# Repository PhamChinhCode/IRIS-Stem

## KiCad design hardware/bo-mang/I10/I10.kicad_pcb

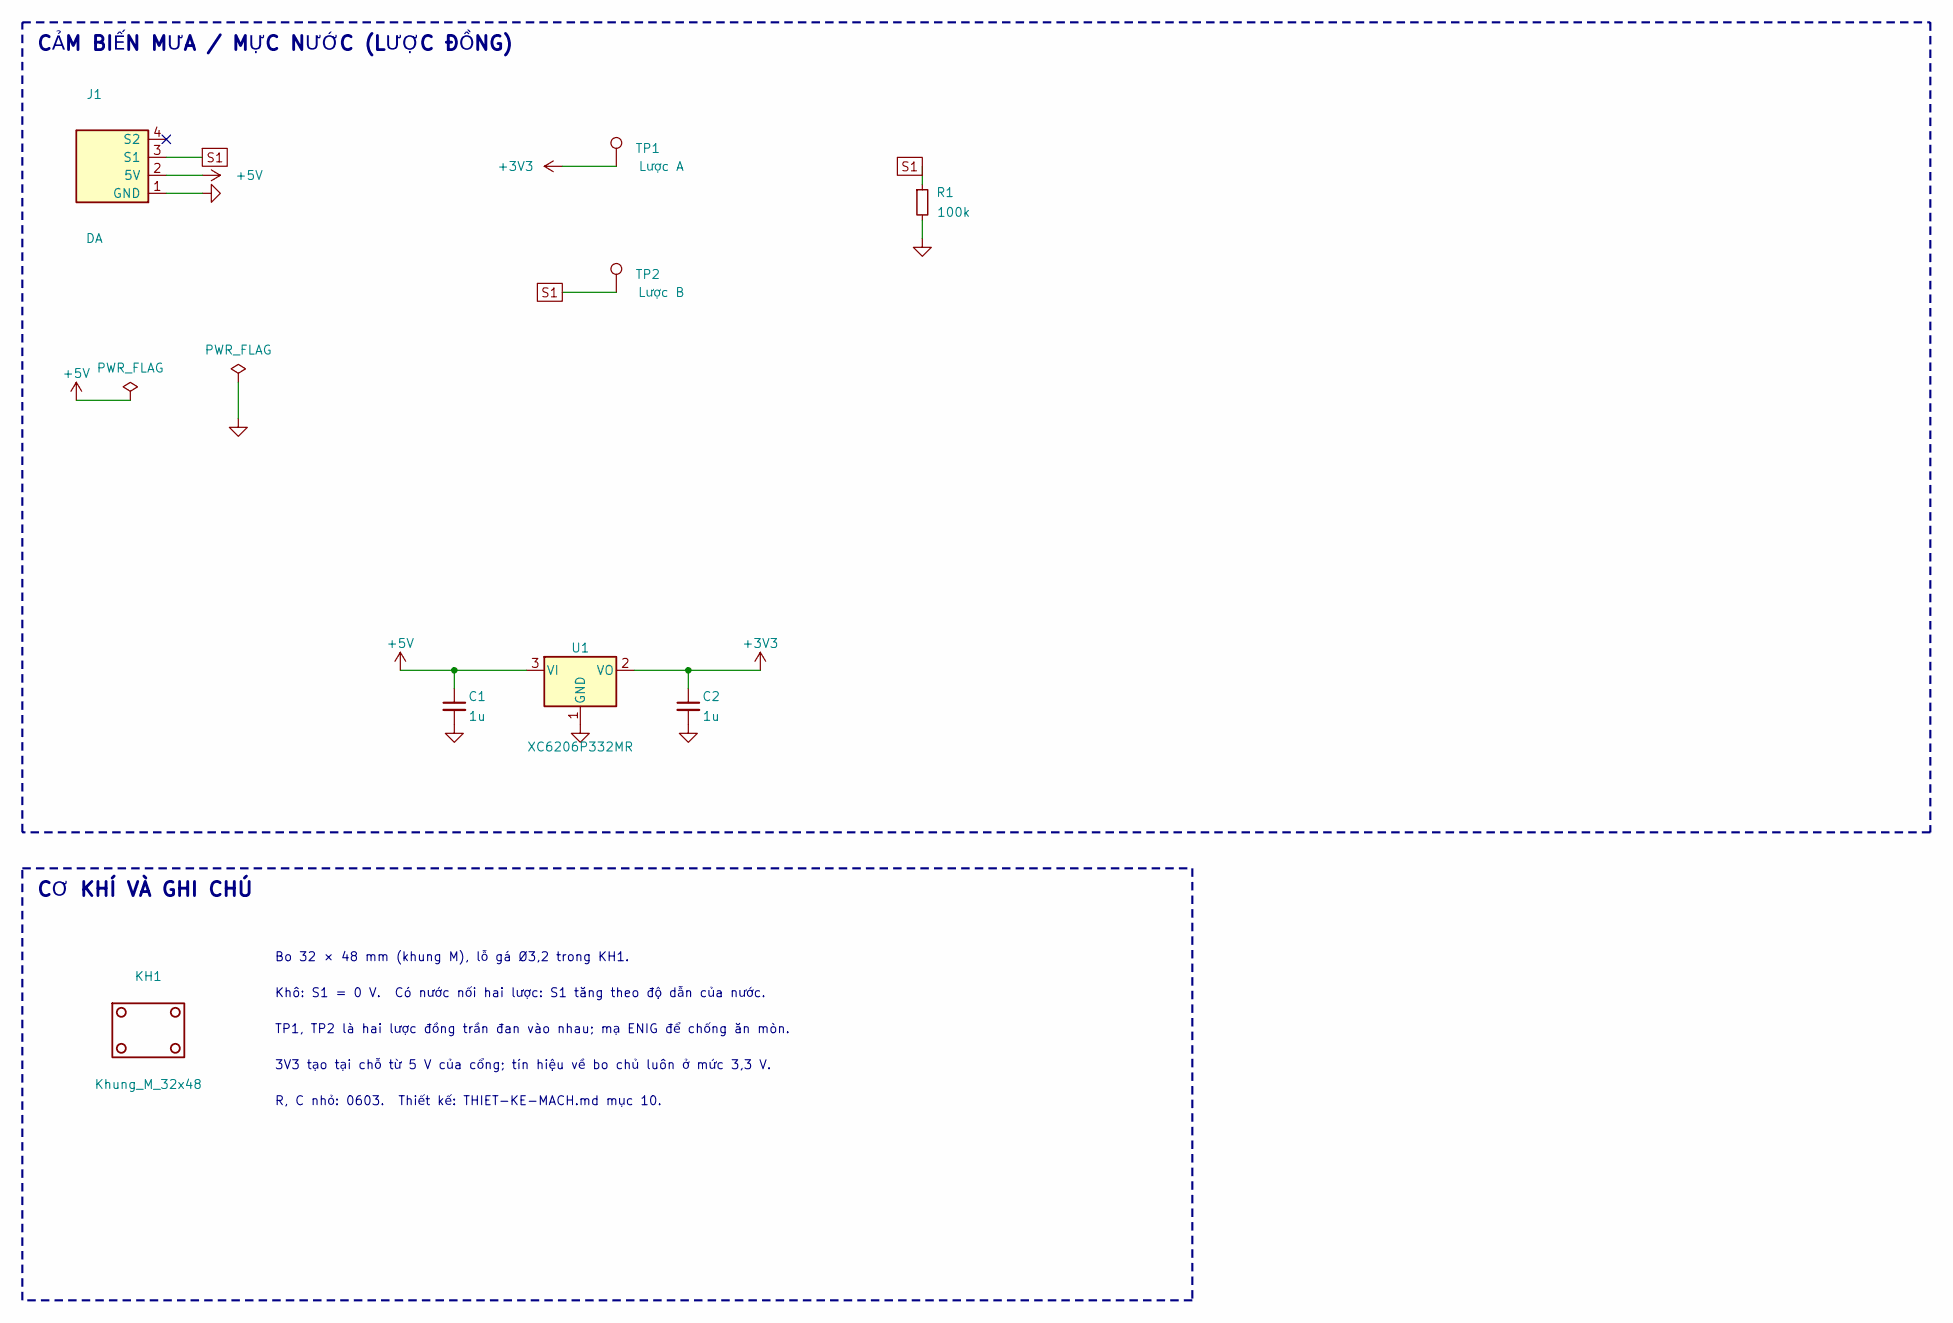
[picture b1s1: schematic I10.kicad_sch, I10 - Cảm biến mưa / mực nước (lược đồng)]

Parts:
C1, C2: 1u; C_0603_1608Metric
J1: DA; Cong_PH_4P_Ngang
KH1: Khung_M_32x48
R1: 100k; R_0603_1608Metric
TP1: Lược A; TestPoint_Pad_D1.5mm
TP2: Lược B; TestPoint_Pad_D1.5mm
U1: XC6206P332MR; SOT-23-3; MPN XC6206P332MR

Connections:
+3V3: C2.1, TP1.1, U1.2 (VO)
+5V: C1.1, J1.2 (5V), U1.3 (VI)
GND: C1.2, C2.2, J1.1 (GND), R1.2, U1.1 (GND)
S1: J1.3 (S1), R1.1, TP2.1

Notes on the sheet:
CẢM BIẾN MƯA / MỰC NƯỚC (LƯỢC ĐỒNG)
CƠ KHÍ VÀ GHI CHÚ
Bo 32 × 48 mm (khung M), lỗ gá Ø3,2 trong KH1.
Khô: S1 = 0 V. Có nước nối hai lược: S1 tăng theo độ dẫn của nước.
TP1, TP2 là hai lược đồng trần đan vào nhau; mạ ENIG để chống ăn mòn.
3V3 tạo tại chỗ từ 5 V của cổng; tín hiệu về bo chủ luôn ở mức 3,3 V.
R, C nhỏ: 0603. Thiết kế: THIET-KE-MACH.md mục 10.

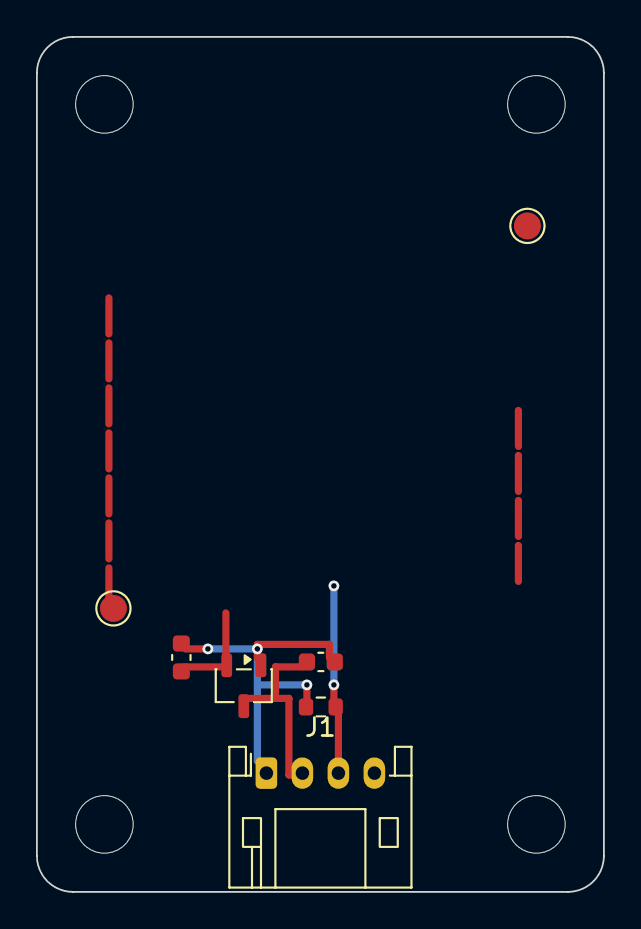
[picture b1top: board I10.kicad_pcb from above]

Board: 2 copper layers, 31.5 x 47.5 mm, 8 parts (0 on the bottom side), 4 nets.

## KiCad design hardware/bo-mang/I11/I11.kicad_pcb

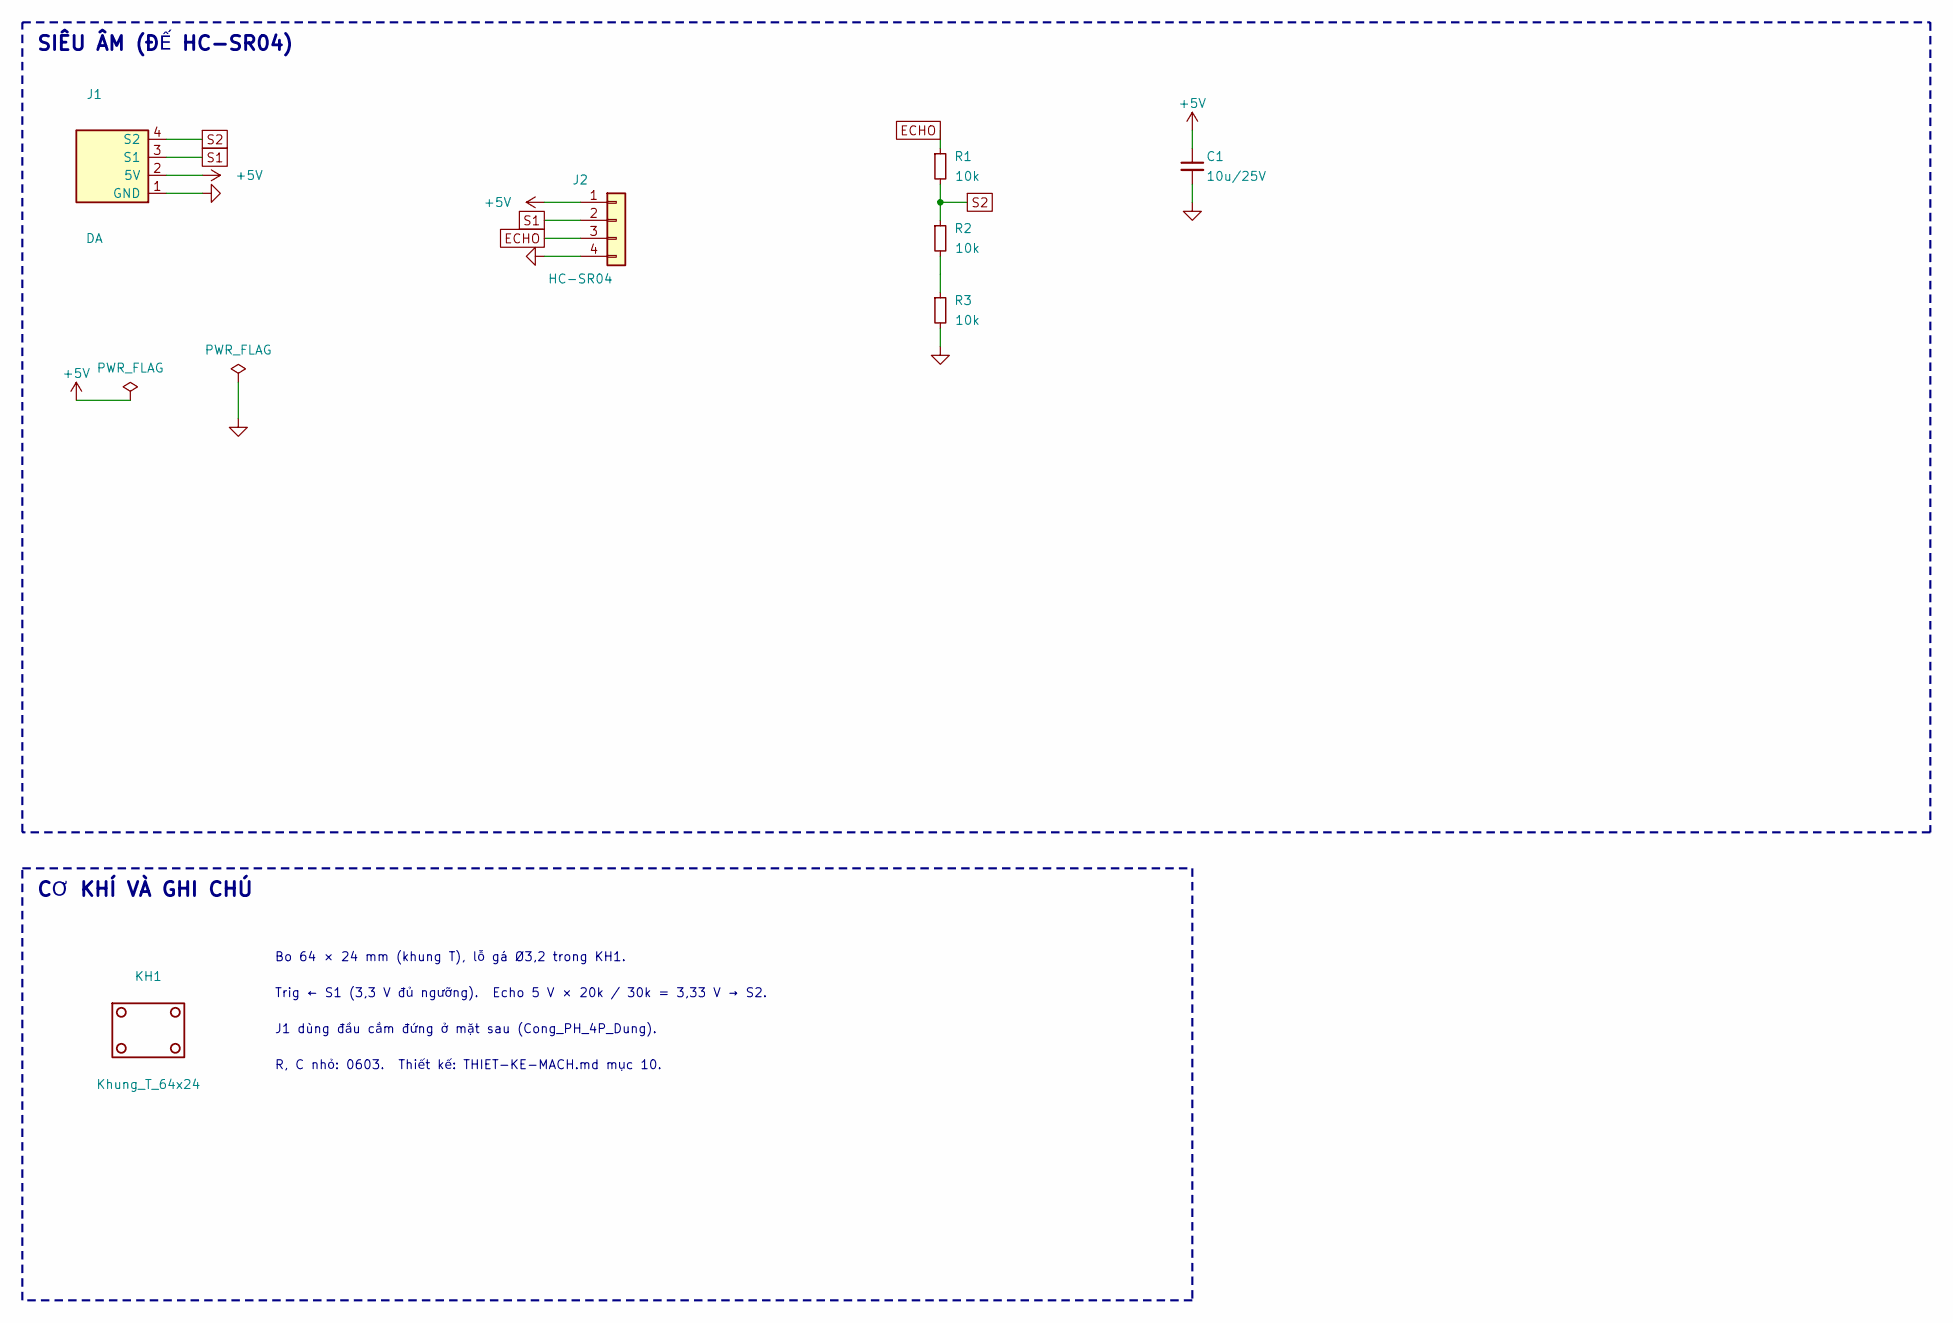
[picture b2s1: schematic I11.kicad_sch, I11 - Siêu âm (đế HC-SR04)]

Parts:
C1: 10u/25V; C_0805_2012Metric
J1: DA; Cong_PH_4P_Dung
J2: HC-SR04; PinSocket_1x04_P2.54mm_Vertical
KH1: Khung_T_64x24
R1, R2, R3: 10k; R_0603_1608Metric

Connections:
+5V: C1.1, J1.2 (5V), J2.1
ECHO: J2.3, R1.1
GND: C1.2, J1.1 (GND), J2.4, R3.2
unnamed: R2.2, R3.1
S1: J1.3 (S1), J2.2
S2: J1.4 (S2), R1.2, R2.1

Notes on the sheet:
SIÊU ÂM (ĐẾ HC-SR04)
CƠ KHÍ VÀ GHI CHÚ
Bo 64 × 24 mm (khung T), lỗ gá Ø3,2 trong KH1.
Trig ← S1 (3,3 V đủ ngưỡng). Echo 5 V × 20k / 30k = 3,33 V → S2.
J1 dùng đầu cắm đứng ở mặt sau (Cong_PH_4P_Dung).
R, C nhỏ: 0603. Thiết kế: THIET-KE-MACH.md mục 10.

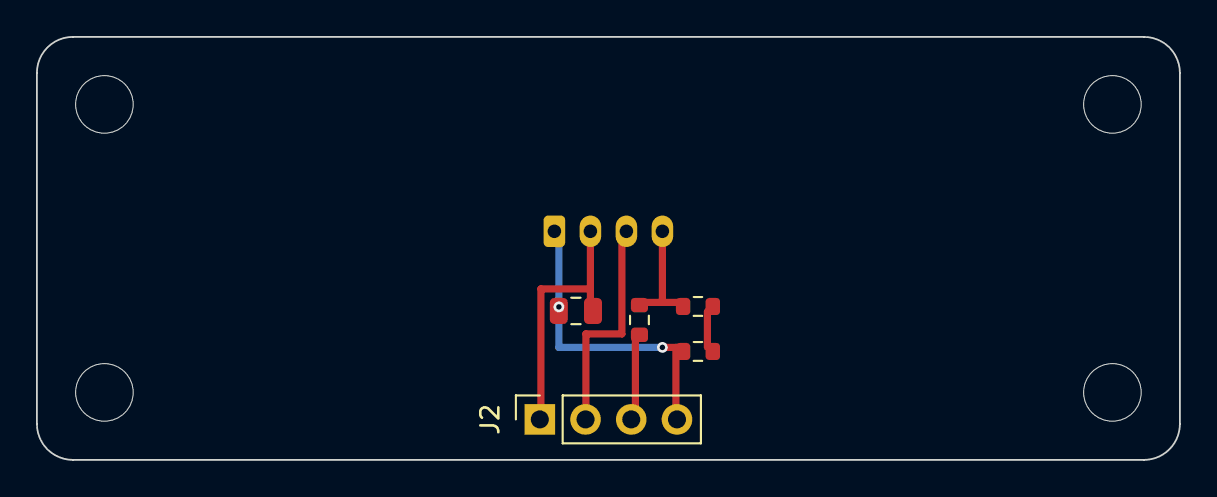
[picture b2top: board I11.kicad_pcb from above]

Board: 2 copper layers, 63.5 x 23.5 mm, 7 parts (1 on the bottom side), 6 nets.

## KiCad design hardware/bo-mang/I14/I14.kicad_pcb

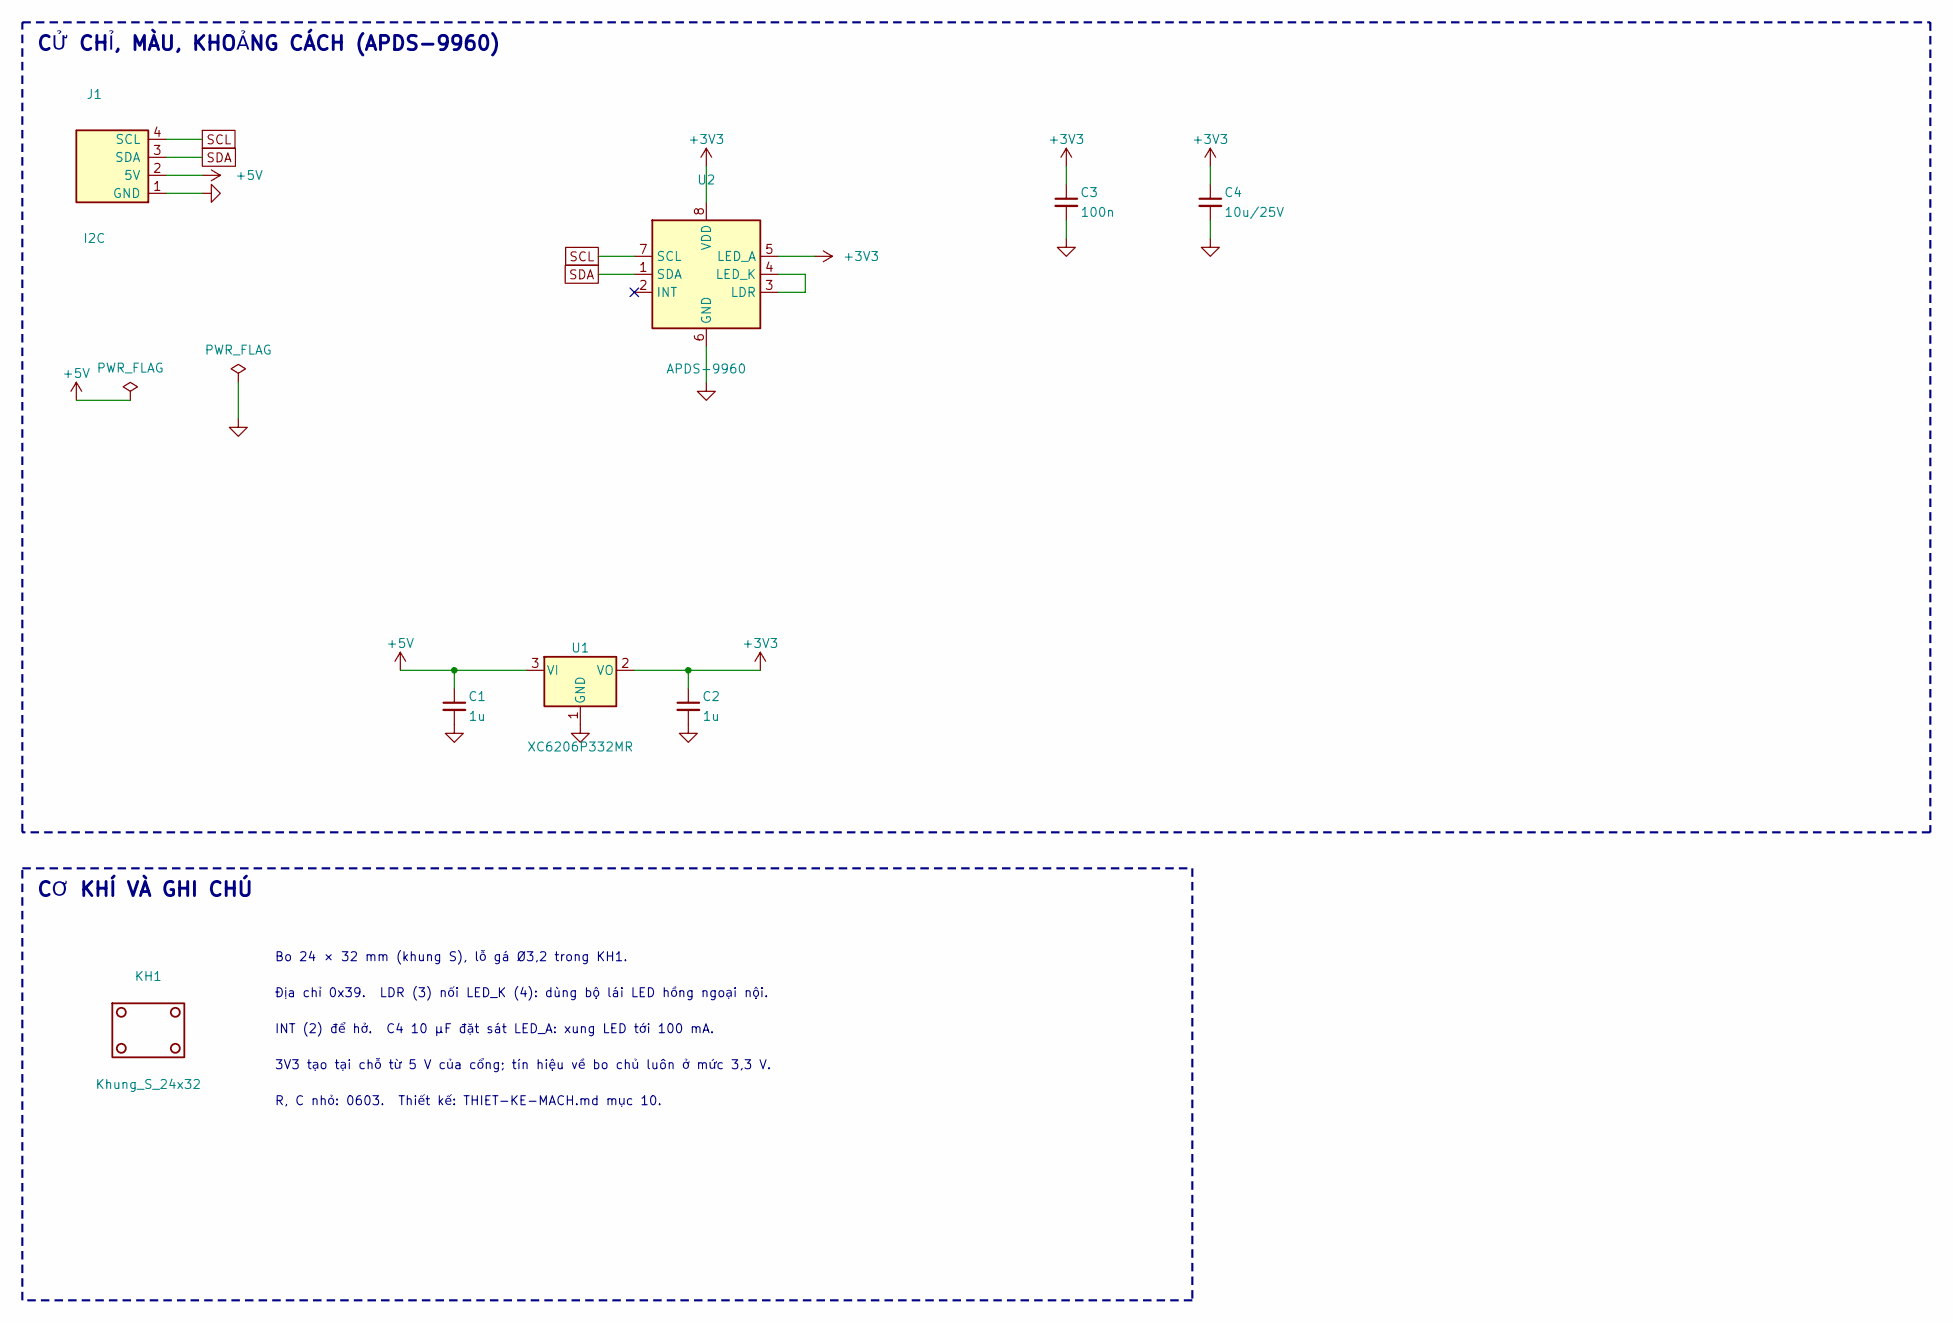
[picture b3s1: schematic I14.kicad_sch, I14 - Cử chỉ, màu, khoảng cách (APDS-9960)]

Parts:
C1, C2: 1u; C_0603_1608Metric
C3: 100n; C_0603_1608Metric
C4: 10u/25V; C_0805_2012Metric
J1: I2C; Cong_PH_4P_Ngang
KH1: Khung_S_24x32
U1: XC6206P332MR; SOT-23-3; MPN XC6206P332MR
U2: APDS-9960; Avago_APDS-9960; MPN APDS-9960

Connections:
+3V3: C2.1, C3.1, C4.1, U1.2 (VO), U2.5 (LED_A), U2.8 (VDD)
+5V: C1.1, J1.2 (5V), U1.3 (VI)
GND: C1.2, C2.2, C3.2, C4.2, J1.1 (GND), U1.1 (GND), U2.6 (GND)
unnamed: U2.3 (LDR), U2.4 (LED_K)
SCL: J1.4 (SCL), U2.7 (SCL)
SDA: J1.3 (SDA), U2.1 (SDA)

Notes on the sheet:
CỬ CHỈ, MÀU, KHOẢNG CÁCH (APDS-9960)
CƠ KHÍ VÀ GHI CHÚ
Bo 24 × 32 mm (khung S), lỗ gá Ø3,2 trong KH1.
Địa chỉ 0x39. LDR (3) nối LED_K (4): dùng bộ lái LED hồng ngoại nội.
INT (2) để hở. C4 10 µF đặt sát LED_A: xung LED tới 100 mA.
3V3 tạo tại chỗ từ 5 V của cổng; tín hiệu về bo chủ luôn ở mức 3,3 V.
R, C nhỏ: 0603. Thiết kế: THIET-KE-MACH.md mục 10.

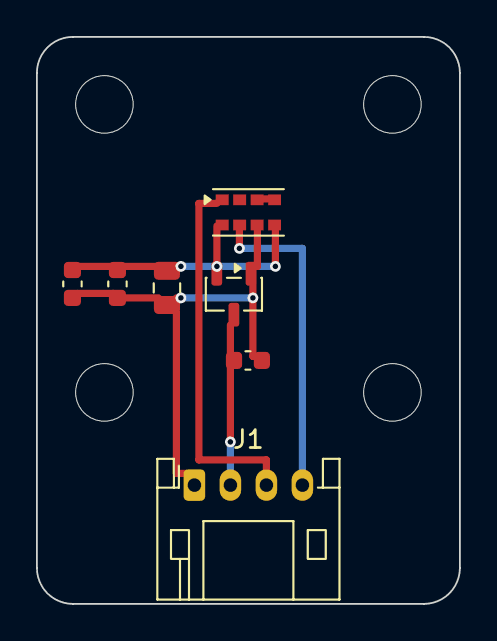
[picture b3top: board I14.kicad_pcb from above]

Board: 2 copper layers, 23.5 x 31.5 mm, 8 parts (0 on the bottom side), 6 nets.

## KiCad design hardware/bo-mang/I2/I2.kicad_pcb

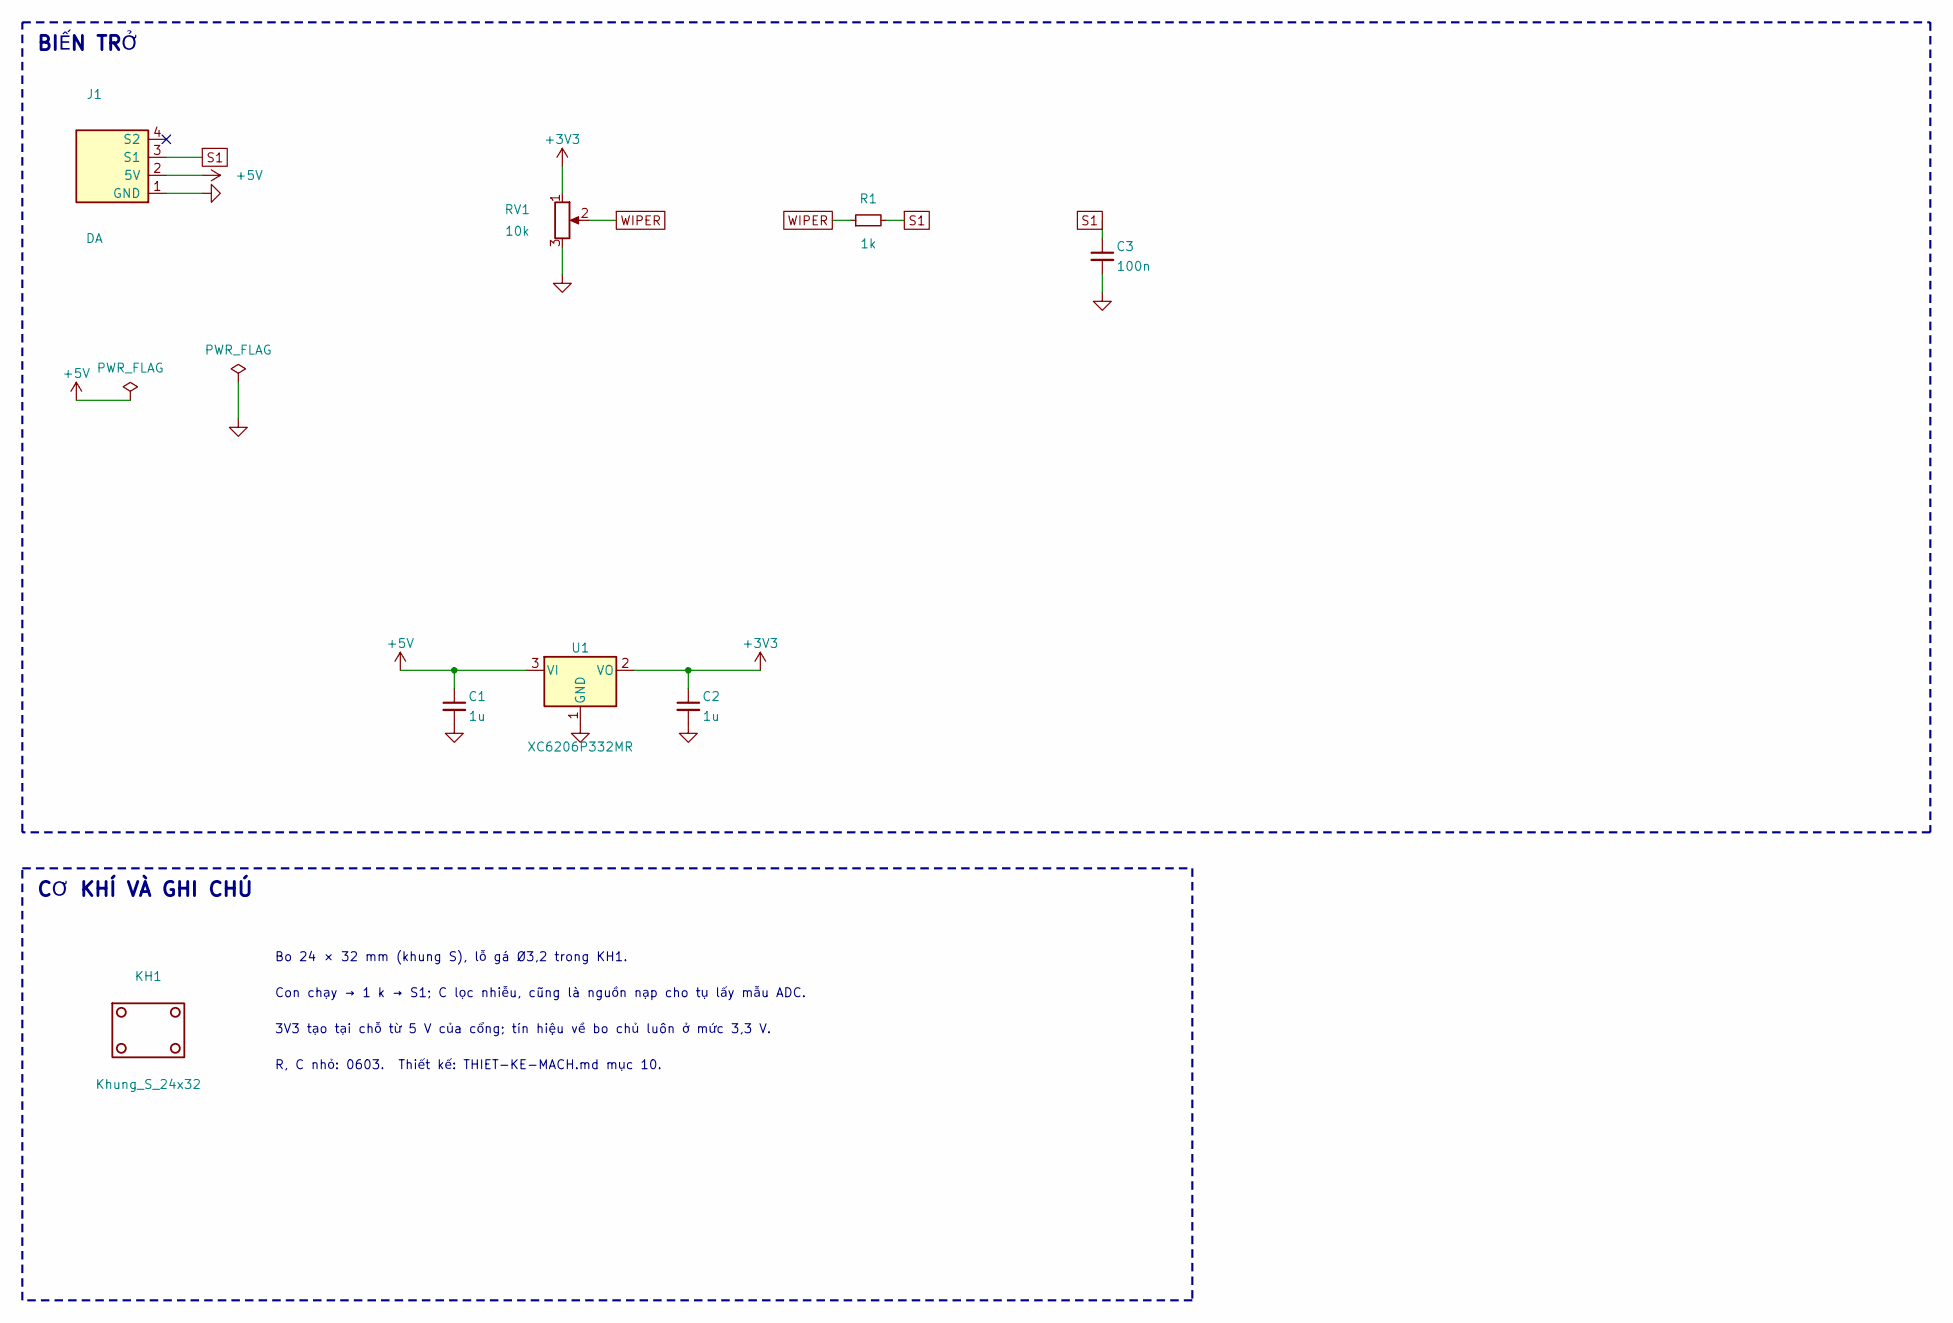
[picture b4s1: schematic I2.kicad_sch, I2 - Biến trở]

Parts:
C1, C2: 1u; C_0603_1608Metric
C3: 100n; C_0603_1608Metric
J1: DA; Cong_PH_4P_Ngang
KH1: Khung_S_24x32
R1: 1k; R_0603_1608Metric
RV1: 10k; Potentiometer_Alps_RK09K_Single_Vertical
U1: XC6206P332MR; SOT-23-3; MPN XC6206P332MR

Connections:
+3V3: C2.1, RV1.1, U1.2 (VO)
+5V: C1.1, J1.2 (5V), U1.3 (VI)
GND: C1.2, C2.2, C3.2, J1.1 (GND), RV1.3, U1.1 (GND)
S1: C3.1, J1.3 (S1), R1.2
WIPER: R1.1, RV1.2

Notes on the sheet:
BIẾN TRỞ
CƠ KHÍ VÀ GHI CHÚ
Bo 24 × 32 mm (khung S), lỗ gá Ø3,2 trong KH1.
Con chạy → 1 k → S1; C lọc nhiễu, cũng là nguồn nạp cho tụ lấy mẫu ADC.
3V3 tạo tại chỗ từ 5 V của cổng; tín hiệu về bo chủ luôn ở mức 3,3 V.
R, C nhỏ: 0603. Thiết kế: THIET-KE-MACH.md mục 10.

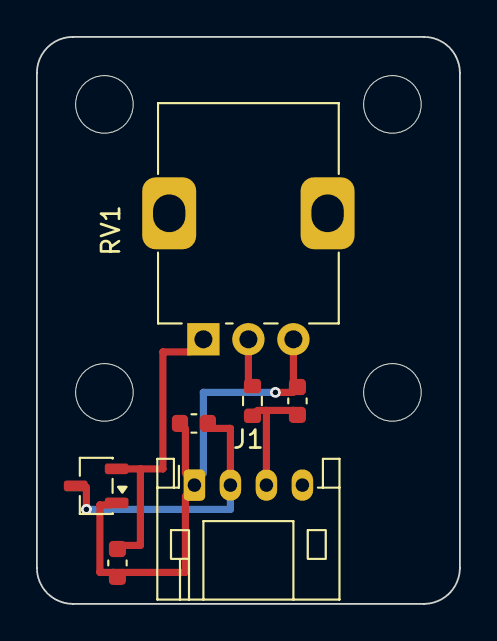
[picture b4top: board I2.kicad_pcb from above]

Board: 2 copper layers, 23.5 x 31.5 mm, 8 parts (0 on the bottom side), 5 nets.

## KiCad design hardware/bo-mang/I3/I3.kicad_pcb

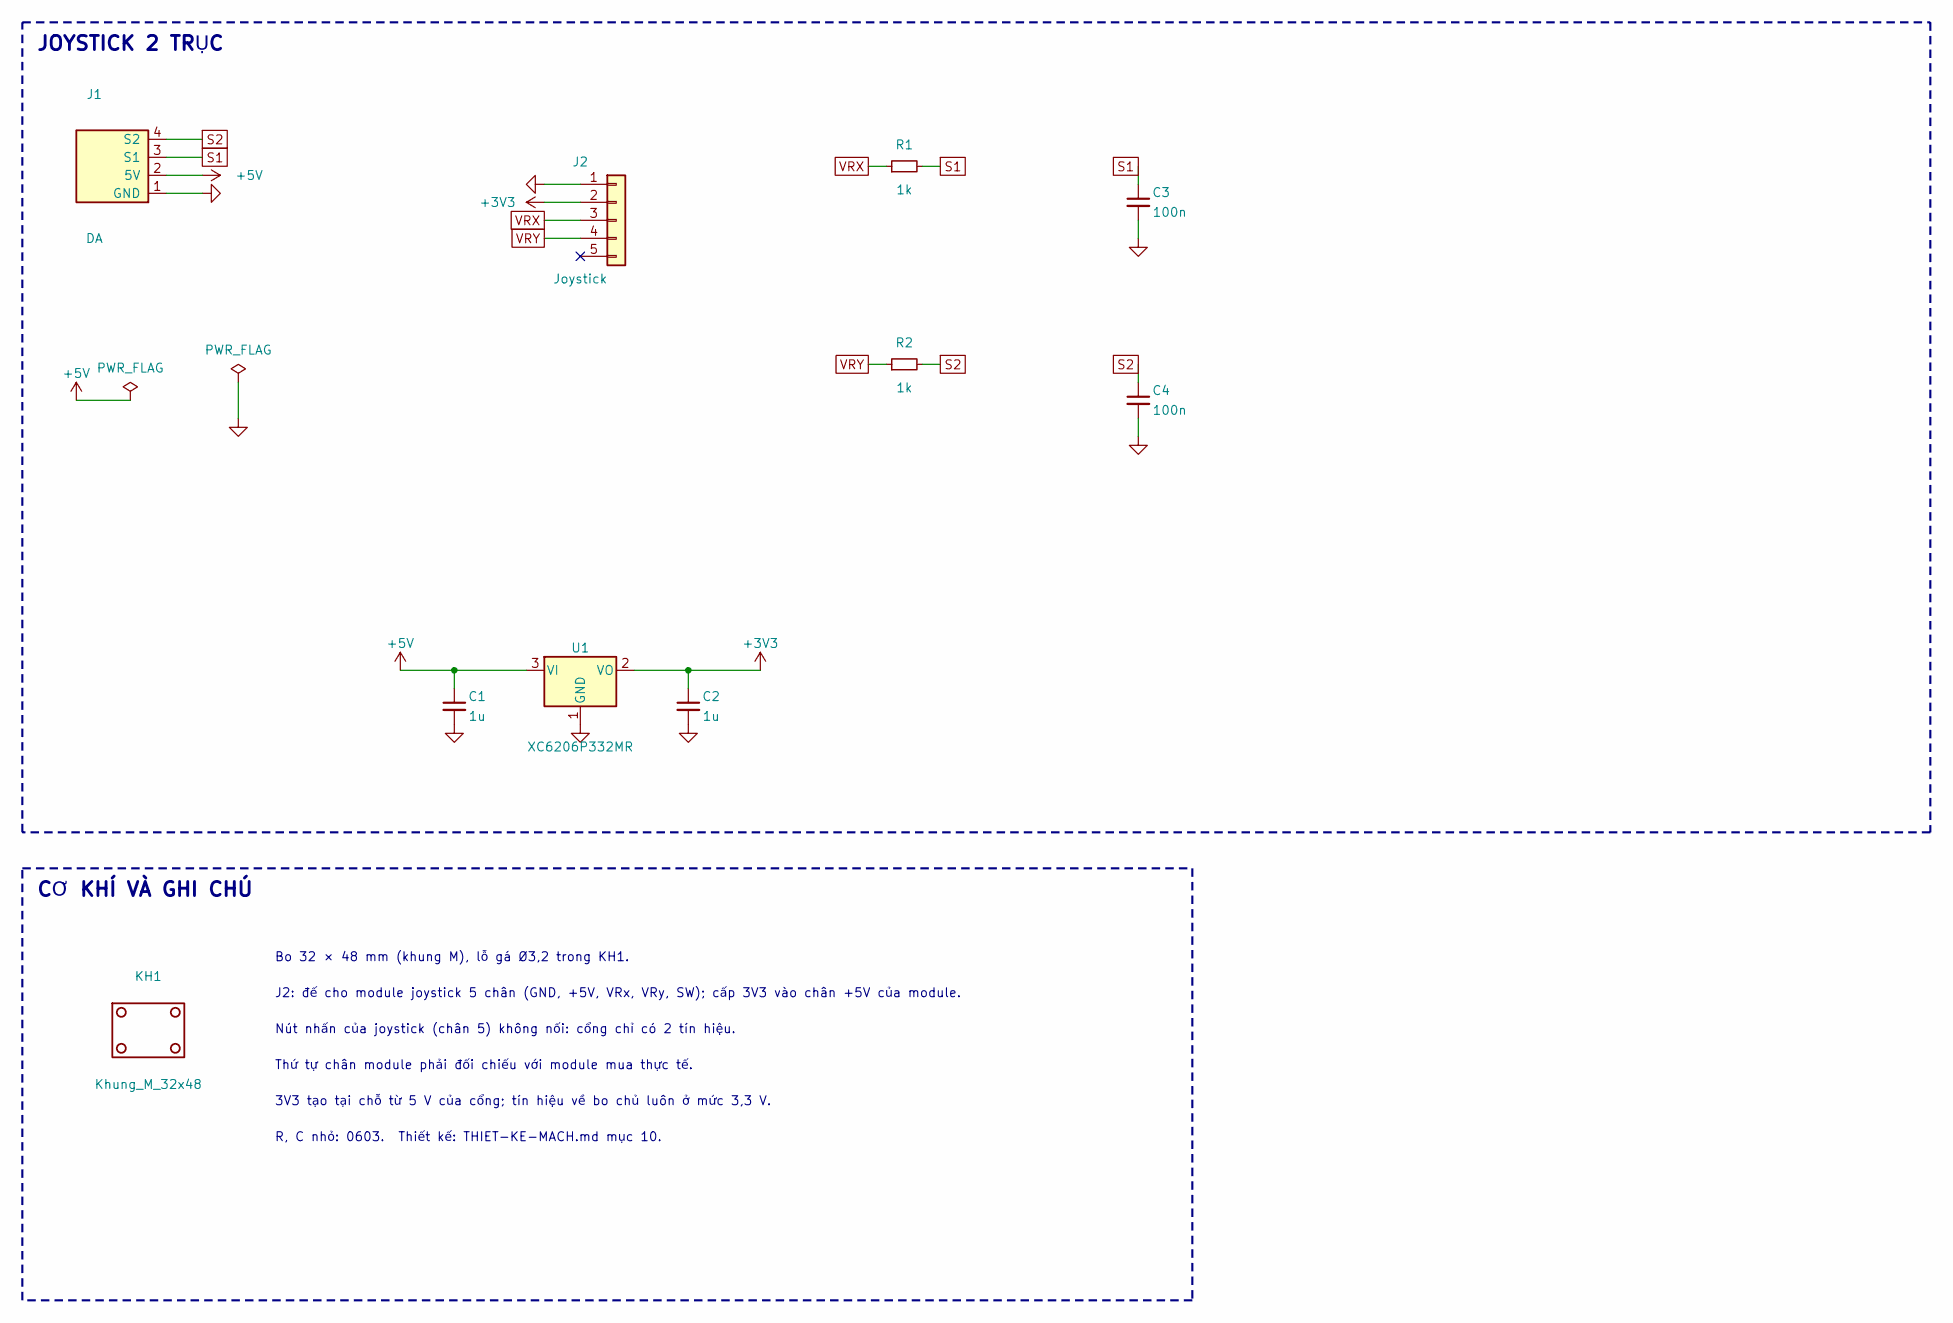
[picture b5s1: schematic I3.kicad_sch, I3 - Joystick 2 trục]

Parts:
C1, C2: 1u; C_0603_1608Metric
C3, C4: 100n; C_0603_1608Metric
J1: DA; Cong_PH_4P_Ngang
J2: Joystick; PinSocket_1x05_P2.54mm_Vertical
KH1: Khung_M_32x48
R1, R2: 1k; R_0603_1608Metric
U1: XC6206P332MR; SOT-23-3; MPN XC6206P332MR

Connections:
+3V3: C2.1, J2.2, U1.2 (VO)
+5V: C1.1, J1.2 (5V), U1.3 (VI)
GND: C1.2, C2.2, C3.2, C4.2, J1.1 (GND), J2.1, U1.1 (GND)
S1: C3.1, J1.3 (S1), R1.2
S2: C4.1, J1.4 (S2), R2.2
VRX: J2.3, R1.1
VRY: J2.4, R2.1

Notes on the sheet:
JOYSTICK 2 TRỤC
CƠ KHÍ VÀ GHI CHÚ
Bo 32 × 48 mm (khung M), lỗ gá Ø3,2 trong KH1.
J2: đế cho module joystick 5 chân (GND, +5V, VRx, VRy, SW); cấp 3V3 vào chân +5V của module.
Nút nhấn của joystick (chân 5) không nối: cổng chỉ có 2 tín hiệu.
Thứ tự chân module phải đối chiếu với module mua thực tế.
3V3 tạo tại chỗ từ 5 V của cổng; tín hiệu về bo chủ luôn ở mức 3,3 V.
R, C nhỏ: 0603. Thiết kế: THIET-KE-MACH.md mục 10.

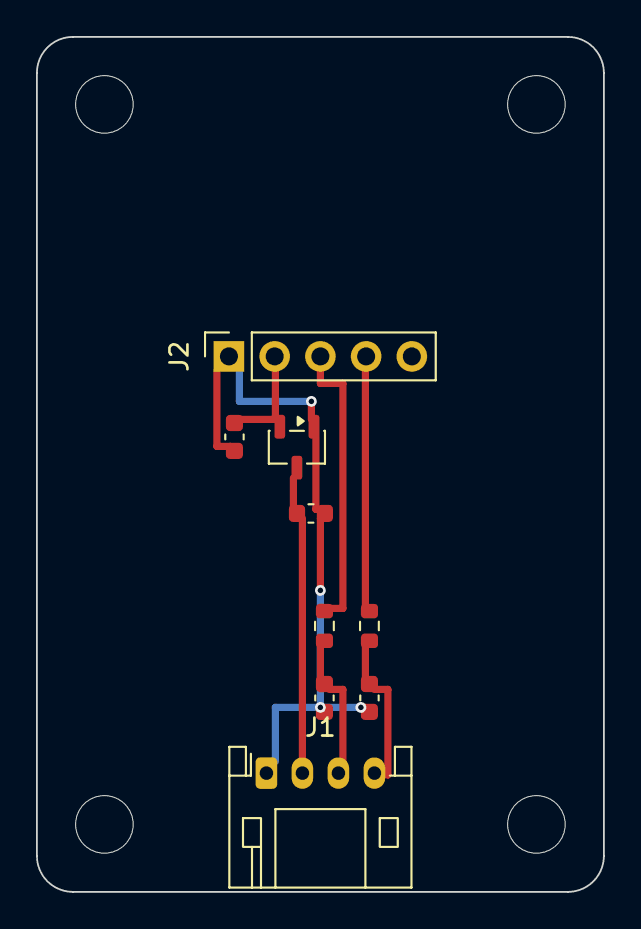
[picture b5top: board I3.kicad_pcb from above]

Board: 2 copper layers, 31.5 x 47.5 mm, 10 parts (0 on the bottom side), 7 nets.

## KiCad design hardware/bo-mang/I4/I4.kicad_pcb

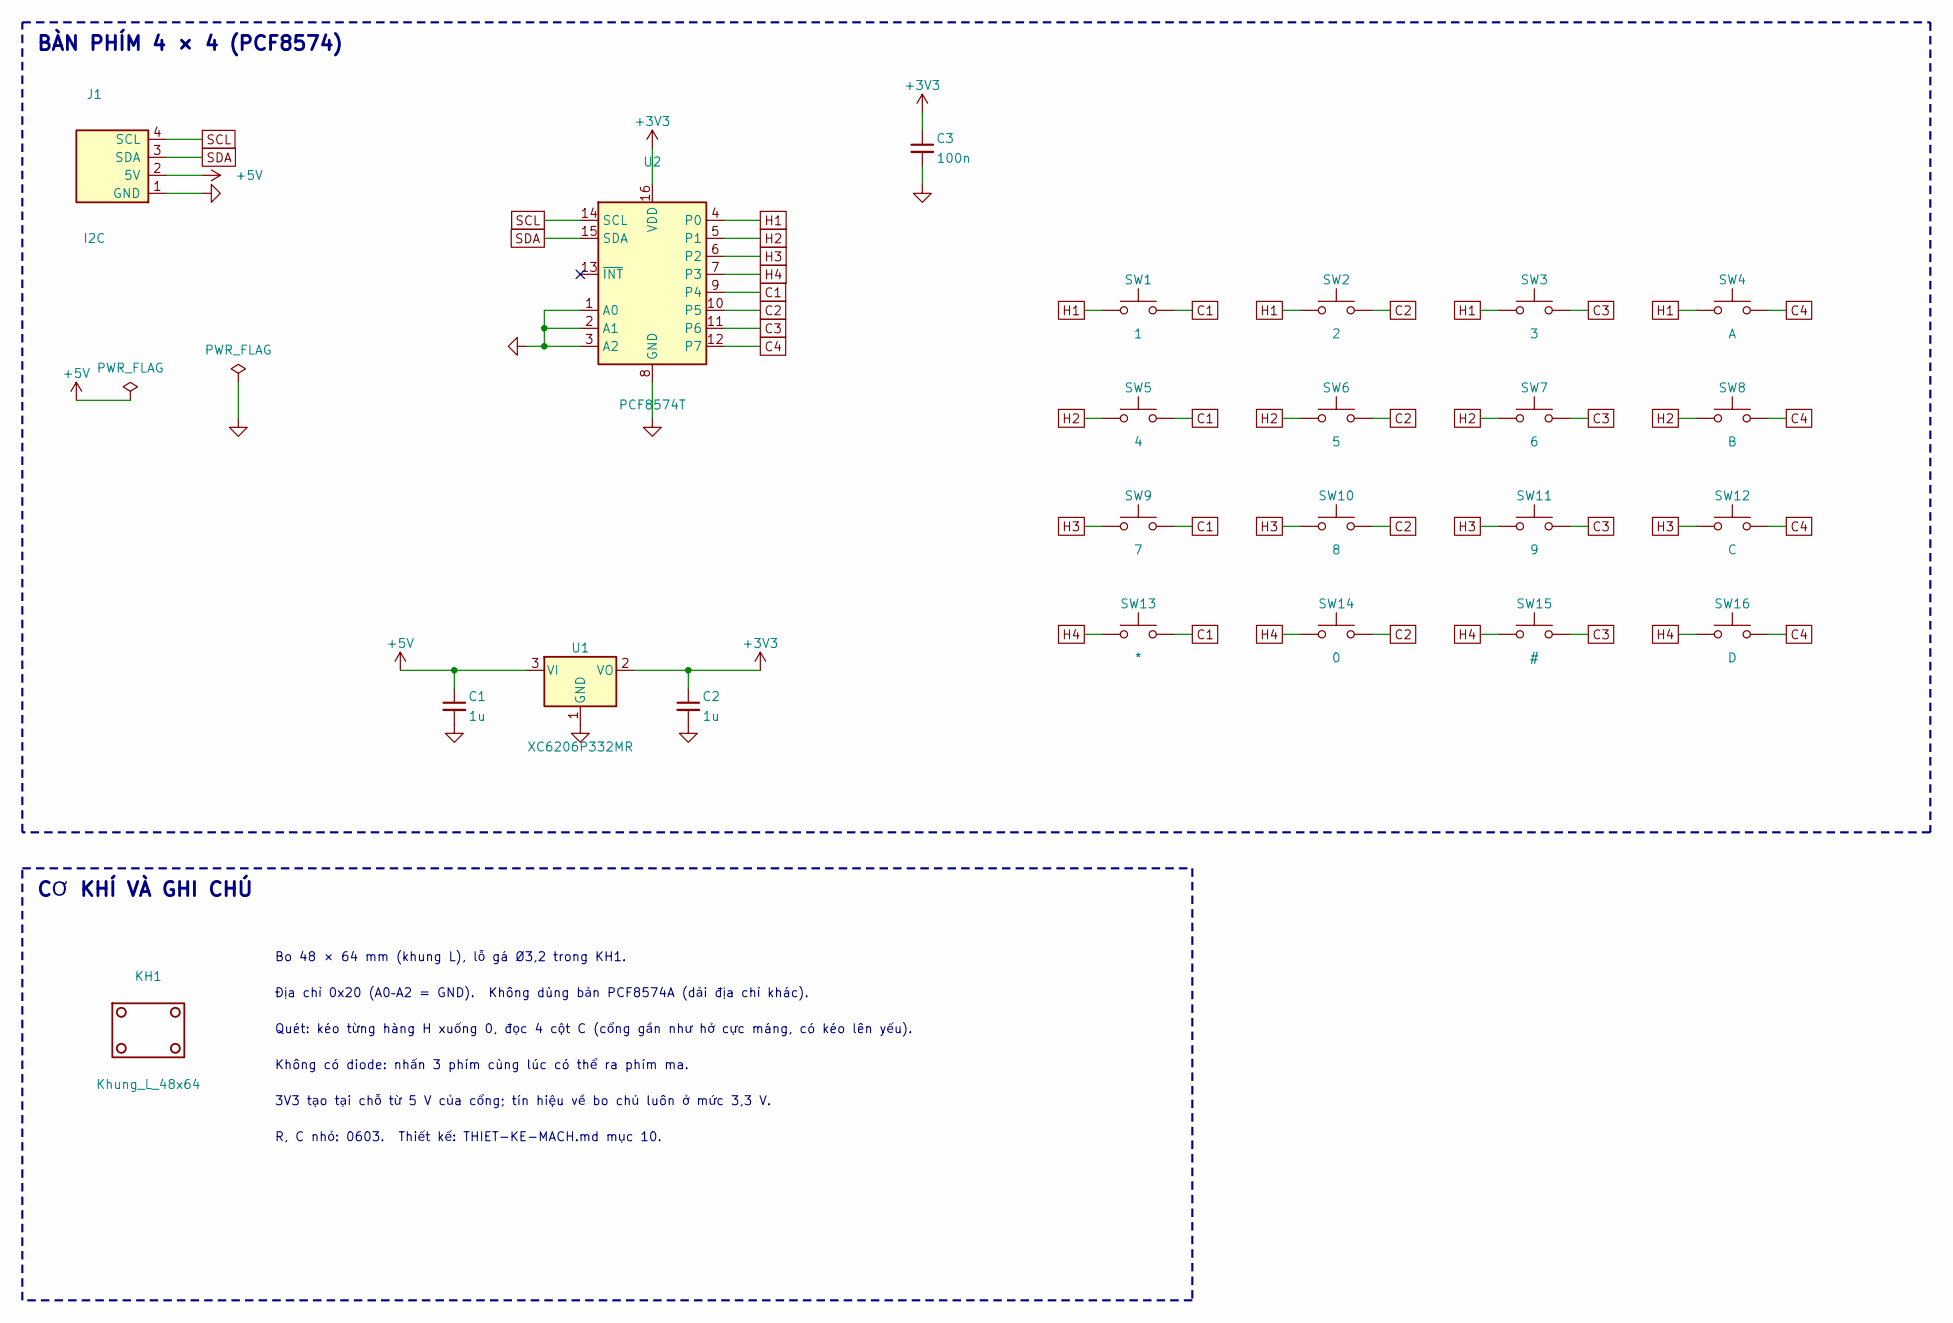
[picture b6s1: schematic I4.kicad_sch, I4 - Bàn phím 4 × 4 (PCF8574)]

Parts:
C1, C2: 1u; C_0603_1608Metric
C3: 100n; C_0603_1608Metric
J1: I2C; Cong_PH_4P_Ngang
KH1: Khung_L_48x64
SW1: 1; SW_Push_1TS009xxxx-xxxx-xxxx_6x6x5mm
SW2: 2; SW_Push_1TS009xxxx-xxxx-xxxx_6x6x5mm
SW3: 3; SW_Push_1TS009xxxx-xxxx-xxxx_6x6x5mm
SW4: A; SW_Push_1TS009xxxx-xxxx-xxxx_6x6x5mm
SW5: 4; SW_Push_1TS009xxxx-xxxx-xxxx_6x6x5mm
SW6: 5; SW_Push_1TS009xxxx-xxxx-xxxx_6x6x5mm
SW7: 6; SW_Push_1TS009xxxx-xxxx-xxxx_6x6x5mm
SW8: B; SW_Push_1TS009xxxx-xxxx-xxxx_6x6x5mm
SW9: 7; SW_Push_1TS009xxxx-xxxx-xxxx_6x6x5mm
SW10: 8; SW_Push_1TS009xxxx-xxxx-xxxx_6x6x5mm
SW11: 9; SW_Push_1TS009xxxx-xxxx-xxxx_6x6x5mm
SW12: C; SW_Push_1TS009xxxx-xxxx-xxxx_6x6x5mm
SW13: *; SW_Push_1TS009xxxx-xxxx-xxxx_6x6x5mm
SW14: 0; SW_Push_1TS009xxxx-xxxx-xxxx_6x6x5mm
SW15: #; SW_Push_1TS009xxxx-xxxx-xxxx_6x6x5mm
SW16: D; SW_Push_1TS009xxxx-xxxx-xxxx_6x6x5mm
U1: XC6206P332MR; SOT-23-3; MPN XC6206P332MR
U2: PCF8574T; SOIC-16W_7.5x10.3mm_P1.27mm; MPN PCF8574T

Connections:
+3V3: C2.1, C3.1, U1.2 (VO), U2.16 (VDD)
+5V: C1.1, J1.2 (5V), U1.3 (VI)
C1: SW1.2, SW5.2, SW9.2, SW13.2, U2.9 (P4)
C2: SW2.2, SW6.2, SW10.2, SW14.2, U2.10 (P5)
C3: SW3.2, SW7.2, SW11.2, SW15.2, U2.11 (P6)
C4: SW4.2, SW8.2, SW12.2, SW16.2, U2.12 (P7)
GND: C1.2, C2.2, C3.2, J1.1 (GND), U1.1 (GND), U2.1 (A0), U2.2 (A1), U2.3 (A2), U2.8 (GND)
H1: SW1.1, SW2.1, SW3.1, SW4.1, U2.4 (P0)
H2: SW5.1, SW6.1, SW7.1, SW8.1, U2.5 (P1)
H3: SW9.1, SW10.1, SW11.1, SW12.1, U2.6 (P2)
H4: SW13.1, SW14.1, SW15.1, SW16.1, U2.7 (P3)
SCL: J1.4 (SCL), U2.14 (SCL)
SDA: J1.3 (SDA), U2.15 (SDA)

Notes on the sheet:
BÀN PHÍM 4 × 4 (PCF8574)
CƠ KHÍ VÀ GHI CHÚ
Bo 48 × 64 mm (khung L), lỗ gá Ø3,2 trong KH1.
Địa chỉ 0x20 (A0–A2 = GND). Không dùng bản PCF8574A (dải địa chỉ khác).
Quét: kéo từng hàng H xuống 0, đọc 4 cột C (cổng gần như hở cực máng, có kéo lên yếu).
Không có diode: nhấn 3 phím cùng lúc có thể ra phím ma.
3V3 tạo tại chỗ từ 5 V của cổng; tín hiệu về bo chủ luôn ở mức 3,3 V.
R, C nhỏ: 0603. Thiết kế: THIET-KE-MACH.md mục 10.

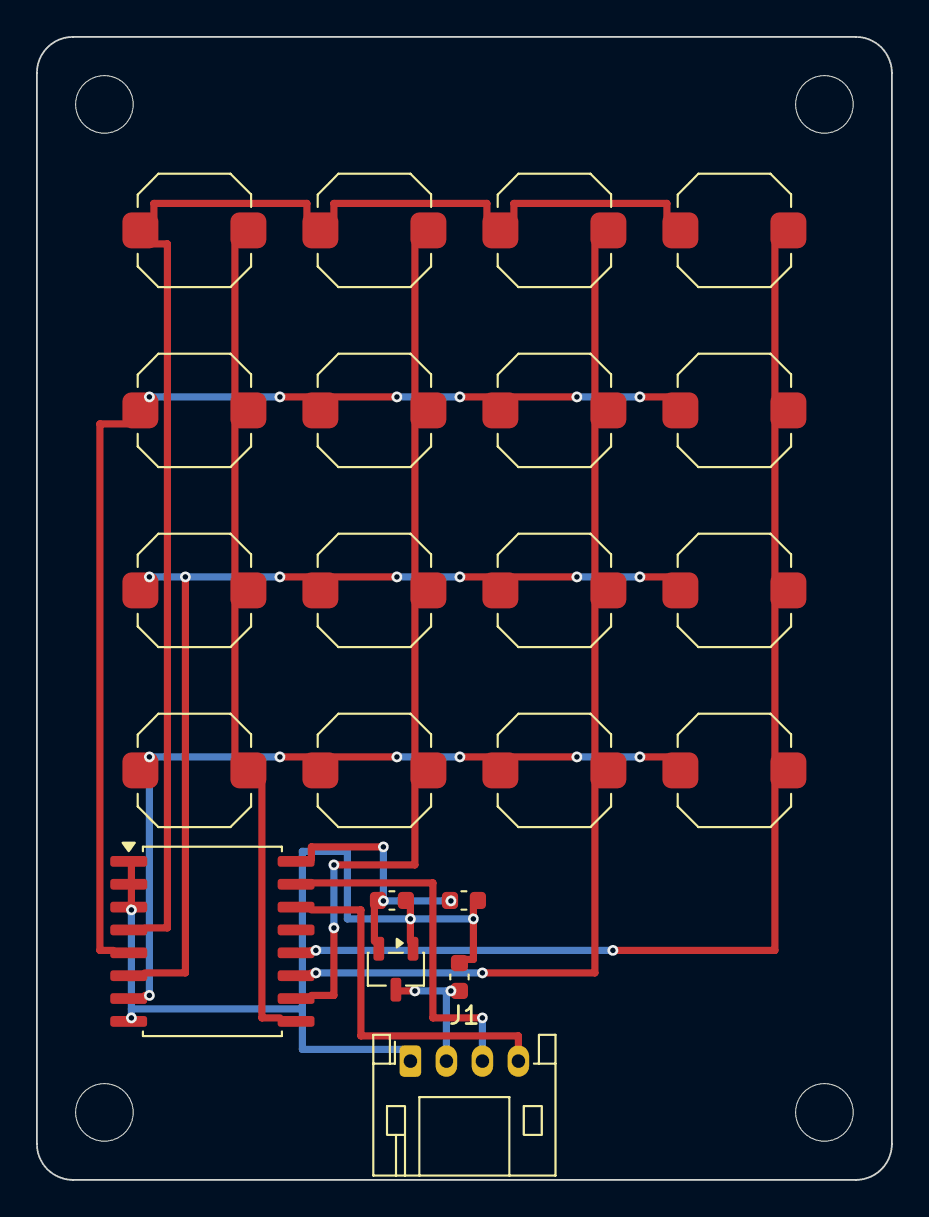
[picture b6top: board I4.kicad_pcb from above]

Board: 2 copper layers, 47.5 x 63.5 mm, 23 parts (0 on the bottom side), 13 nets.
